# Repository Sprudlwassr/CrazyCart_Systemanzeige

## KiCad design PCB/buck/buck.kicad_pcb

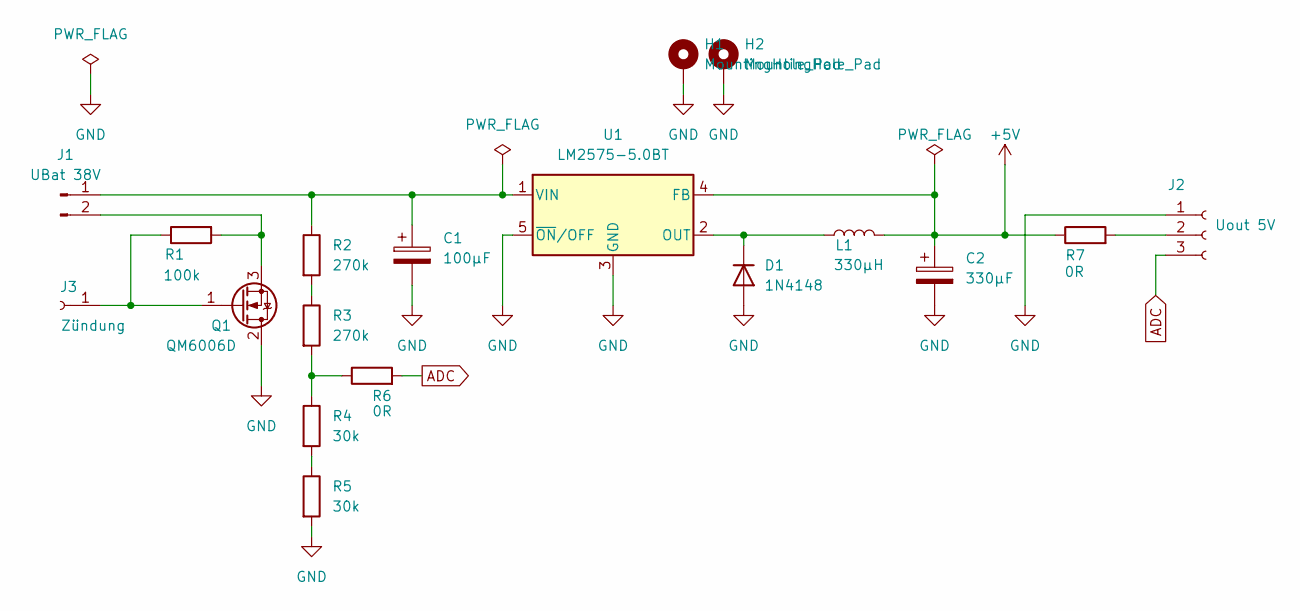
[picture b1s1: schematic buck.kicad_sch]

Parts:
C1: 100µF; CP_Elec_8x10
C2: 330µF; CP_Elec_10x10.5
D1: 1N4148; D_0805_2012Metric_Pad1.15x1.40mm_HandSolder
H1, H2: MountingHole_Pad; MountingHole_2.7mm_M2.5_Pad
J1: UBat 38V; PinSocket_1x02_P2.54mm_Horizontal
J2: Uout 5V; PinSocket_1x03_P2.54mm_Horizontal
J3: Zündung; PinSocket_1x01_P2.54mm_Horizontal
L1: 330µH; L_12x12mm_H8mm
Q1: QM6006D; TO-252-2
R1: 100k; R_0805_2012Metric
R2, R3: 270k; R_0805_2012Metric
R4, R5: 30k; R_0805_2012Metric
R6, R7: 0R; R_0603_1608Metric
U1: LM2575-5.0BT; TO-220-5_Vertical

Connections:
+5V: C2.1, L1.2, R7.1, U1.4 (FB)
ADC: J2.3, R6.2
GND: C1.2, C2.2, D1.1 (A), H1.1, H2.1, J2.1, Q1.2 (D), R5.2, U1.3 (GND), U1.5 (~ON/OFF)
unnamed: C1.1, J1.1, R2.1, U1.1 (VIN)
unnamed: D1.2 (K), L1.1, U1.2 (OUT)
unnamed: J1.2, Q1.3 (S), R1.2
unnamed: J2.2, R7.2
unnamed: J3.1, Q1.1 (G), R1.1
unnamed: R2.2, R3.1
unnamed: R3.2, R4.1, R6.1
unnamed: R4.2, R5.1

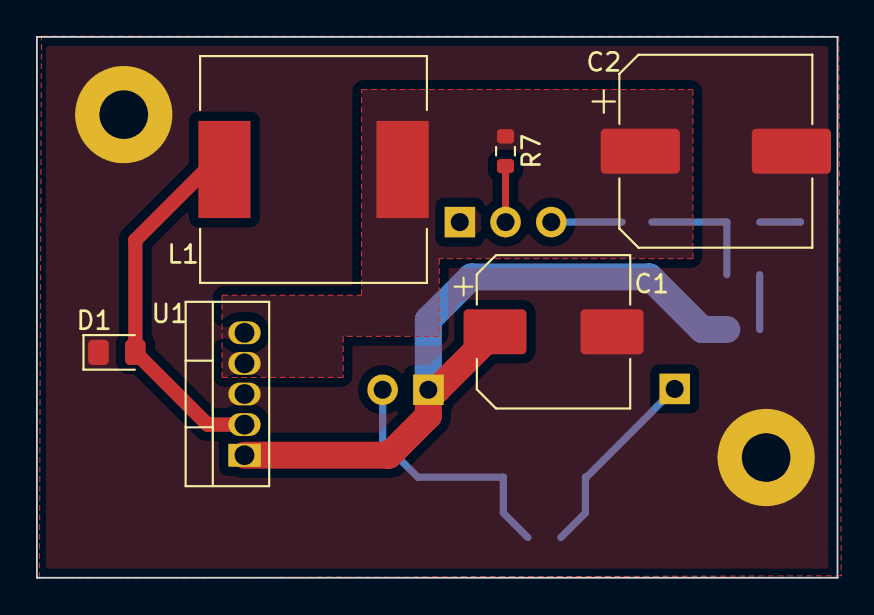
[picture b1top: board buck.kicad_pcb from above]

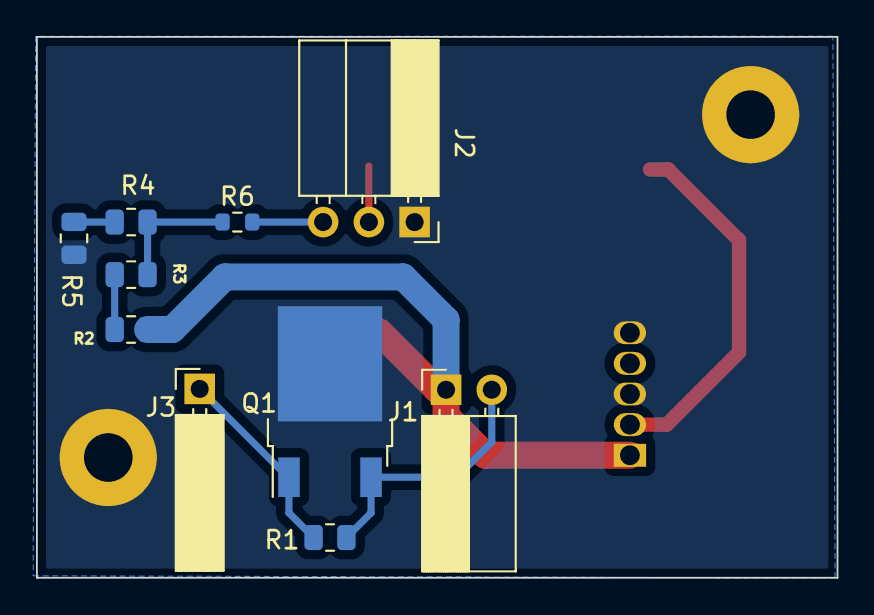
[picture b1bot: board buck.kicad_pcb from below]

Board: 2 copper layers, 44.5 x 30.0 mm, 18 parts (10 on the bottom side), 11 nets.

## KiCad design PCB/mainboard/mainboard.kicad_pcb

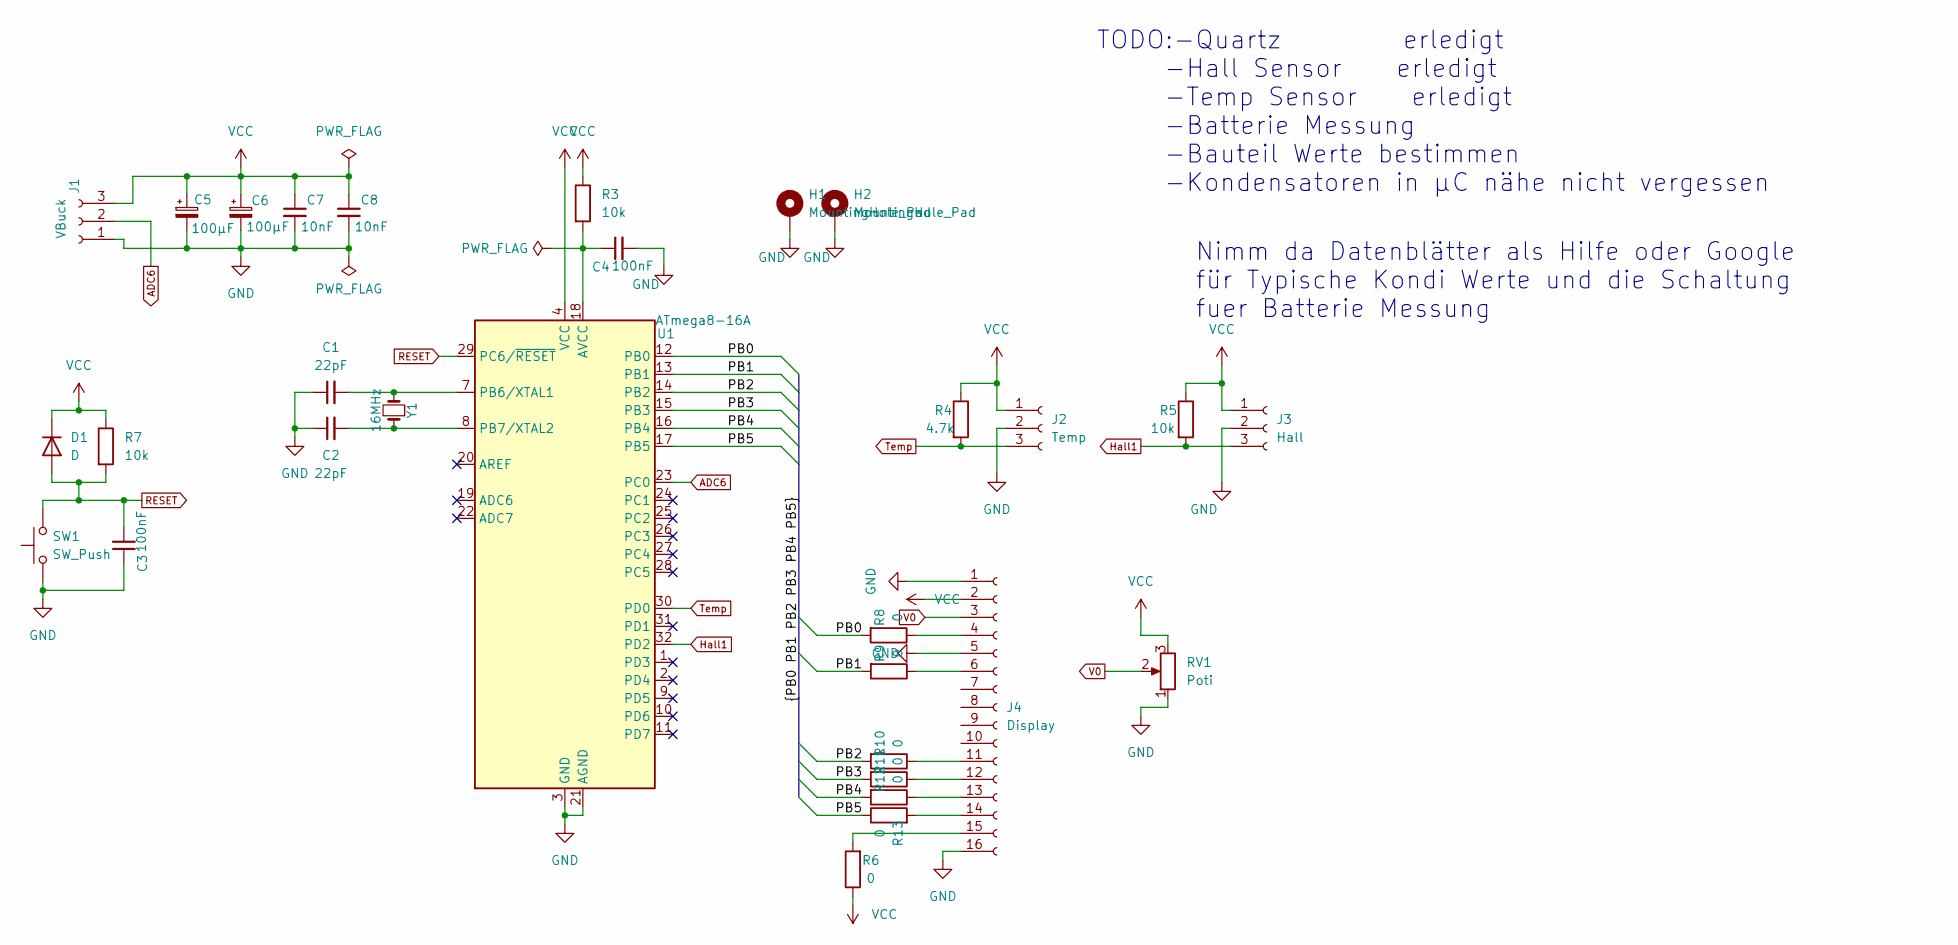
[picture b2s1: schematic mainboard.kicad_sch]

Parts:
C1, C2: 22pF; C_0805_2012Metric
C3, C4: 100nF; C_0805_2012Metric
C5, C6: 100µF; CP_Elec_5x5.8
C7, C8: 10nF; C_0603_1608Metric
D1: D; D_0805_2012Metric
H1, H2: MountingHole_Pad; MountingHole_2.7mm_M2.5_Pad
J1: VBuck; PinSocket_1x03_P2.54mm_Vertical
J2: Temp; PinSocket_1x03_P2.54mm_Horizontal
J3: Hall; PinSocket_1x03_P2.54mm_Horizontal
J4: Display; PinSocket_1x16_P2.54mm_Vertical
R3, R5, R7: 10k; R_0805_2012Metric
R4: 4.7k; R_0805_2012Metric
R6, R8, R9, R10, R11, R12, R13: 0; R_0805_2012Metric
RV1: Poti; Potentiometer_Bourns_3314G_Vertical
SW1: SW_Push; SW_PUSH_6mm
U1: ATmega8-16A; TQFP-32_7x7mm_P0.8mm
Y1: 16MHz; Crystal_SMD_ECS_CSM3X-2Pin_7.6x4.1mm

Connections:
/PB0: R8.2, U1.12 (PB0)
/PB1: R9.2, U1.13 (PB1)
/PB2: R10.2, U1.14 (PB2)
/PB3: R11.2, U1.15 (PB3)
/PB4: R12.2, U1.16 (PB4)
/PB5: R13.1, U1.17 (PB5)
ADC6: J1.2, U1.23 (PC0); also elsewhere on the board
GND: C1.1, C2.1, C3.1, C4.2, C5.2, C6.2, C7.2, C8.2, H1.1, H2.1, J1.1, J2.2, J3.2, J4.1, J4.5, J4.16, RV1.1, SW1.1, U1.3 (GND), U1.5 (GND), U1.21 (AGND); also elsewhere on the board
Hall1: J3.3, R5.2, U1.32 (PD2)
unnamed: C1.2, U1.7 (PB6/XTAL1), Y1.2
unnamed: C2.2, U1.8 (PB7/XTAL2), Y1.1
unnamed: C4.1, R3.2, U1.18 (AVCC)
unnamed: J4.4, R8.1
unnamed: J4.6, R9.1
unnamed: J4.11, R10.1
unnamed: J4.12, R11.1
unnamed: J4.13, R12.1
unnamed: J4.14, R13.2
unnamed: J4.15, R6.2
RESET: C3.2, D1.2 (A), R7.2, SW1.2, U1.29 (PC6/~RESET)
Temp: J2.3, R4.2, U1.30 (PD0)
V0: J4.3, RV1.2
VCC: C5.1, C6.1, C7.1, C8.1, D1.1 (K), J1.3, J2.1, J3.1, J4.2, R3.1, R4.1, R5.1, R6.1, R7.1, RV1.3, U1.4 (VCC), U1.6 (VCC); also elsewhere on the board

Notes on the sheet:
TODO:-Quartz erledigt -Hall Sensor erledigt -Temp Sensor erledigt -Batterie Messung -Bauteil Werte bestimmen -Kondensatoren in µC nähe nicht vergessen
Nimm da Datenblätter als Hilfe oder Google für Typische Kondi Werte und die Schaltung fuer Batterie Messung

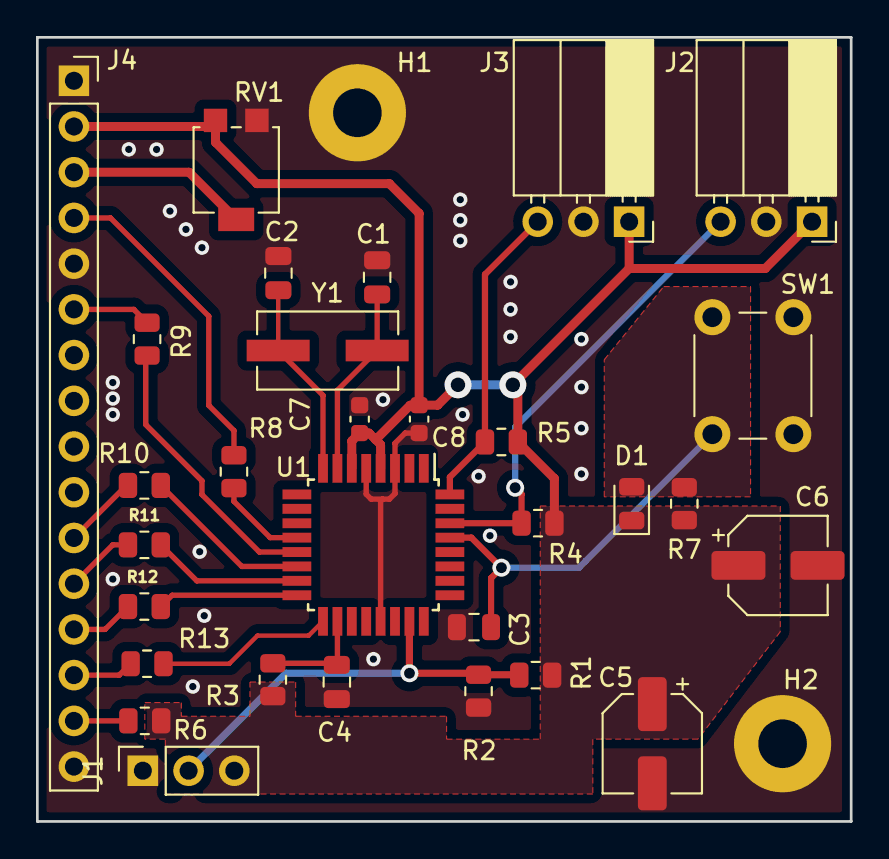
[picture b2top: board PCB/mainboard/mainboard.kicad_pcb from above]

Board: 2 copper layers, 45.2 x 43.6 mm, 32 parts (0 on the bottom side), 23 nets.

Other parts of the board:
R1: 99k; R_0805_2012Metric
R2: 11k; R_0805_2012Metric

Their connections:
ADC6: R1.2, R2.1; also elsewhere on the board
GND: R2.2; also elsewhere on the board
VCC: R1.1; also elsewhere on the board

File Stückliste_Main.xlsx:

|  |  |  |  |  |  |  |  | Höhere technische Bundeslehr- und Versuchsanstalt Rankweil
 |  |  |  |  |  |  |  |  | Abteilung Elektronik
 |  |  |  | Projektname: | Nummer | Betreuungslehrer
 |  |  |  | Alarmanlage 2AFEL 21-22 | n.a. | MM/SCHN
STÜCKLISTE |  |  |  |  |  | SUMME |  | 0
Pos | Stück | Wert | Benennung | Text / Bauform | Quelle | Best.Nr | Preis | Gesamt | Bemerkung
1 | 2 | 22pF | C1,2 | SMD_0805 |  |  |  | 0
2 | 1 | 100nF | C4 | SMD_0805 |  |  |  | 0
3 | 2 | 100µF | C5,6 | SMD_Elco_5x5.8 |  |  |  | 0
4 | 2 | 10nF | C7,8 | SMD_0603 |  |  |  | 0
5 | 1 | Vbuck | J1 | 2.54mm:PinSocket_1x02_Vertical |  |  |  | 0
6 | 2 | Temp,Hall | J2,3 | 2.54mm:PinSocket_1x03_Horizontal |  |  |  | 0
7 | 1 | Display | J4 | 2.54mm:PinSocket_1x16_Vertical |  |  |  | 0
8 | 1 | 99k | R1 | SMD_0805 |  |  |  | 0
9 | 1 | 11k | R2 | SMD_0805 |  |  |  | 0
10 | 2 | 10k | R3,5 | SMD_0805 |  |  |  | 0
11 | 1 | 4.7k | R4 | SMD_0805 |  |  |  | 0
12 | 1 | 0R | R6 | SMD_0805 |  |  |  | 0
13 | 1 | Poti | RV1 | Ppotentiometer_Bourns_3314G_Vertical |  |  |  | 0
14 | 1 | Atmega8-16A | U1 | TQFP-32_7x7mm_P00.8mm |  |  |  | 0
15 | 1 | Y1 | 16MHz | 2pin_7.6x7.1mm |  |  |  | 0
16 |  |  |  |  |  |  |  | 0
17 |  |  |  |  |  |  |  | 0
18 |  |  |  |  |  |  |  | 0
19 |  |  |  |  |  |  |  | 0
20 |  |  |  |  |  |  |  | 0
21 |  |  |  |  |  |  |  | 0
22 |  |  |  |  |  |  |  | 0
23 |  |  |  |  |  |  |  | 0
24 |  |  |  |  |  |  |  | 0
25 |  |  |  |  |  |  |  | 0
26 |  |  |  |  |  |  |  | 0
27 |  |  |  |  |  |  |  | 0
28 |  |  |  |  |  |  |  | 0
29 |  |  |  |  |  |  |  | 0

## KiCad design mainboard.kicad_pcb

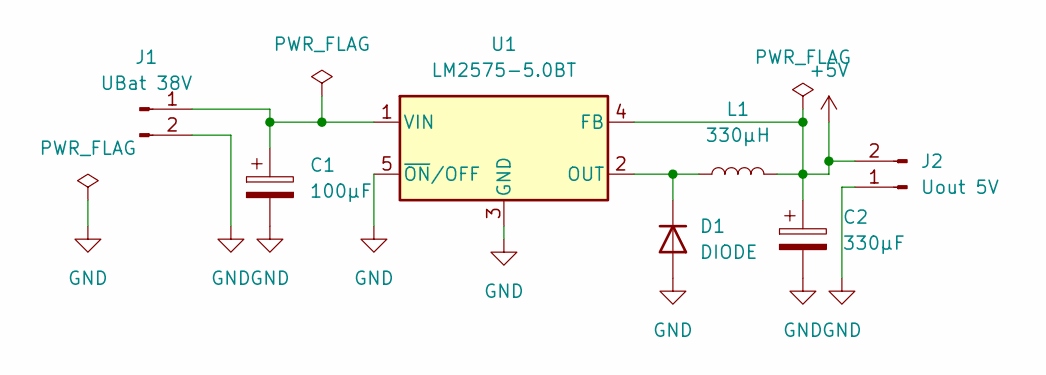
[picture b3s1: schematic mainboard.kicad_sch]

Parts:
C1: 100µF; CP_Elec_8x10
C2: 330µF; CP_Elec_10x10.5
D1: DIODE; D_0805_2012Metric_Pad1.15x1.40mm_HandSolder
J1: UBat 38V; PinHeader_1x02_P2.00mm_Horizontal
J2: Uout 5V; PinHeader_1x02_P2.00mm_Vertical
L1: 330µH; L_12x12mm_H8mm
U1: LM2575-5.0BT; TO-220-5_Vertical

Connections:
+5V: C2.1, J2.2, L1.2, U1.4 (FB)
GND: C1.2, C2.2, D1.1 (A), J1.2, J2.1, U1.3 (GND), U1.5 (~ON/OFF)
unnamed: C1.1, J1.1, U1.1 (VIN)
unnamed: D1.2 (K), L1.1, U1.2 (OUT)

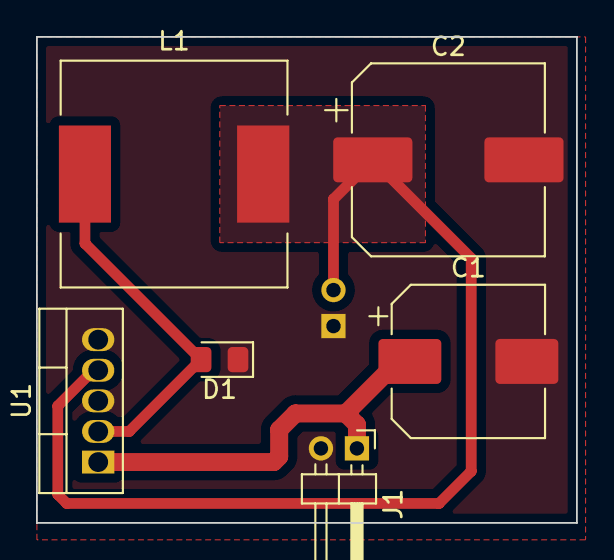
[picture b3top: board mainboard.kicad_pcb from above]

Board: 2 copper layers, 30.0 x 27.0 mm, 7 parts (1 on the bottom side), 4 nets.

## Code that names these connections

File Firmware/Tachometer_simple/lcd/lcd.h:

/* -----------------------------------------
 * G.Raf^engineering
 * www.sunriax.at
 * -----------------------------------------
 *    Platform: Megacard/STK500/STK600
 *    Hardware: ATmega??-????
 * -----------------------------------------
 *     Version: 1.0 Release
 *      Author: G.Raf
 * Description:
 *   Header file for lcd library
 * -----------------------------------------
 */

#ifndef LCD_H_
#define LCD_H_

// Definition of SYSTEM parameters

#ifndef F_CPU           // System clock
    #define F_CPU 12000000UL
#endif

// Definition of LCD parameters

#ifndef F_LCD           // LCD enable clock
    #define F_LCD 100000UL
#endif

// LCD control directives
#ifndef LCD_DDR_CTRL    // LCD control direction register
    #define LCD_DDR_CTRL DDRB
#endif

#ifndef LCD_PORT_CTRL   // LCD control port register
    #define LCD_PORT_CTRL PORTB
#endif

#ifndef LCD_RS          // LCD register select
    #define LCD_RS PB0
#endif

#ifndef LCD_E           // LCD start data read/write
    #define LCD_E PB1
#endif

// LCD data directives
#ifndef LCD_DDR_DATA    // LCD data direction register
    #define LCD_DDR_DATA DDRB
#endif

#ifndef LCD_PORT_DATA   // LCD control direction register
    #define LCD_PORT_DATA PORTB
#endif

#ifndef LCD_DB0         // LCD data bit 0 (LCD display bit 4)
    #define LCD_DB0 PB2
#endif

#ifndef LCD_DB1         // LCD data bit 1 (LCD display bit 5)
    #define LCD_DB1 PB3
#endif

#ifndef LCD_DB2         // LCD data bit 2 (LCD display bit 6)
    #define LCD_DB2 PB4
#endif

#ifndef LCD_DB3         // LCD data bit 3 (LCD display bit 7)
    #define LCD_DB3 PB5
#endif

// LCD display parameters
#ifndef LCD_COLUMNS     // LCD display columns/row (1 - 20)
    #define LCD_COLUMNS 20
#endif

#ifndef LCD_COLUMNS_END     // LCD character memory length
    #define LCD_COLUMNS_END 40
#endif

#ifndef LCD_START_ADDR      // Start position of the LCD RAM
    #define LCD_START_ADDR 0x80
#endif

// LCD time/instruction codes (!!! Do not change !!!)

// LCD time directives
#ifndef LCD_STARTUP_TIME    // LCD startup time in ms
    #define LCD_STARTUP_TIME 10
#endif

#ifndef LCD_RETURN_TIME     // LCD return home time in ms
    #define LCD_RETURN_TIME 2
#endif

#ifndef LCD_ENTRY_TIME      // LCD entry mode time in us
    #define LCD_ENTRY_TIME 37
#endif

// #ifndef LCD_DISPLAY_TIME // LCD display time in us
//  #define LCD_DISPLAY_TIME 37
// #endif

#ifndef LCD_SHIFT_TIME      // LCD shift time in us
    #define LCD_SHIFT_TIME 37
#endif

#ifndef LCD_FUNCTION_TIME   // LCD function time in us
    #define LCD_FUNCTION_TIME 37
#endif

#ifndef LCD_WRITE_TIME      // LCD WRITE time in us
    #define LCD_WRITE_TIME 37
#endif

#ifndef LCD_CMD_TIME        // LCD COMMAND time in us
    #define LCD_CMD_TIME 37
#endif

// LCD instruction directives
#ifndef LCD_CLEAR           // LCD clear display instruction
    #define LCD_CLEAR           0b00000001
#endif

#ifndef LCD_HOME            // LCD return home instruction
    #define LCD_HOME            0b00000010
#endif

#ifndef LCD_ENTRY           // LCD entry mode set instruction
    #define LCD_ENTRY           0b00000100
    #define LCD_ENTRY_INCREMENT 0b00000010
    #define LCD_ENTRY_SHIFT     0b00000001
#endif

#ifndef LCD_DISPLAY         // LCD display set instruction
    #define LCD_DISPLAY         0b00001000
    #define LCD_DISPLAY_ON      0b00000100
    #define LCD_CURSOR_ON       0b00000010
    #define LCD_BLINK_ON        0b00000001
#endif

#ifndef LCD_SHIFT           // LCD shift instruction
    #define LCD_SHIFT           0b00010000
    #define LCD_SHIFT_DISPLAY   0b00001000
    #define LCD_SHIFT_RIGHT     0b00000100
#endif

#ifndef LCD_FUNCTION        // LCD function instruction
    #define LCD_FUNCTION        0b00100000
    #define LCD_FUNCTION_8BIT   0b00010000
    #define LCD_FUNCTION_2LINE  0b00001000
    #define LCD_FUNCTION_5x10   0b00000100
#endif

#ifndef LCD_CGADDR          // LCD CGADDR instruction
    #define LCD_CGADDR          0b01000000
    #define LCD_CGADDR_CHAR0    0b00000000
    #define LCD_CGADDR_CHAR1    0b00000001
    #define LCD_CGADDR_CHAR2    0b00000010
    #define LCD_CGADDR_CHAR3    0b00000011
    #define LCD_CGADDR_CHAR4    0b00000100
    #define LCD_CGADDR_CHAR5    0b00000101
    #define LCD_CGADDR_CHAR6    0b00000110
    #define LCD_CGADDR_CHAR7    0b00000111
    #define LCD_CGADDDR_MAX     7
#endif

#ifndef LCD_DDADDR          // LCD DDADDR instruction
    #define LCD_DDADDR          0b10000000
#endif

#ifndef LCD_SPACE           // Space character
    #define LCD_SPACE 0x20
#endif

#ifndef LCD_NULL            // End character
    #define LCD_NULL 0x00
#endif

#include <stdlib.h>
#include <avr/io.h>
#include <util/delay.h>

enum LCD_Shift_t
{
    LCD_Right=0,
    LCD_Left
};
typedef enum LCD_Shift_t LCD_Shift;

enum LCD_Base_t
{
    LCD_Binary=2,
    LCD_Decimal=10,
    LCD_Hexadecimal=16    
};
typedef enum LCD_Base_t LCD_Base;

enum LCD_Char_t
{
    LCD_Char0=LCD_CGADDR_CHAR0,
    LCD_Char1=LCD_CGADDR_CHAR1,
    LCD_Char2=LCD_CGADDR_CHAR2,
    LCD_Char3=LCD_CGADDR_CHAR3,
    LCD_Char4=LCD_CGADDR_CHAR4,
    LCD_Char5=LCD_CGADDR_CHAR5,
    LCD_Char6=LCD_CGADDR_CHAR6,
    LCD_Char7=LCD_CGADDR_CHAR7
};
typedef enum LCD_Char_t LCD_Char;

void lcd_init(void);
void lcd_disable(void);
void lcd_clock(void);
void lcd_set(unsigned char data);
void lcd_cmd(unsigned char instruction);
void lcd_char(unsigned char data);
void lcd_string(const char *data);
void lcd_clear(void);
void lcd_home(void);
void lcd_cursor(unsigned char x, unsigned char y);
void lcd_shift(LCD_Shift shift);
void lcd_pattern(LCD_Char address, const unsigned char *data);
void lcd_ul2ascii(unsigned long data, LCD_Base base, unsigned char length);
void lcd_sl2ascii(const signed long data, LCD_Base base, unsigned char length);
void lcd_d2ascii(const double data, signed char length, unsigned char precision);

#endif /* LCD_H_ */

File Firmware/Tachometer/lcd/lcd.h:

/* -----------------------------------------
 * G.Raf^engineering
 * www.sunriax.at
 * -----------------------------------------
 *    Platform: Megacard/STK500/STK600
 *    Hardware: ATmega??-????
 * -----------------------------------------
 *     Version: 1.0 Release
 *      Author: G.Raf
 * Description:
 *   Header file for lcd library
 * -----------------------------------------
 */

#ifndef LCD_H_
#define LCD_H_

// Definition of SYSTEM parameters

#ifndef F_CPU           // System clock
    #define F_CPU 12000000UL
#endif

// Definition of LCD parameters

#ifndef F_LCD           // LCD enable clock
    #define F_LCD 100000UL
#endif

// LCD control directives
#ifndef LCD_DDR_CTRL    // LCD control direction register
    #define LCD_DDR_CTRL DDRA
#endif

#ifndef LCD_PORT_CTRL   // LCD control port register
    #define LCD_PORT_CTRL PORTA
#endif

#ifndef LCD_RS          // LCD register select
    #define LCD_RS PA6
#endif

#ifndef LCD_E           // LCD start data read/write
    #define LCD_E PA4
#endif

// LCD data directives
#ifndef LCD_DDR_DATA    // LCD data direction register
    #define LCD_DDR_DATA DDRB
#endif

#ifndef LCD_PORT_DATA   // LCD control direction register
    #define LCD_PORT_DATA PORTB
#endif

#ifndef LCD_DB0         // LCD data bit 0 (LCD display bit 4)
    #define LCD_DB0 PB2
#endif

#ifndef LCD_DB1         // LCD data bit 1 (LCD display bit 5)
    #define LCD_DB1 PB5
#endif

#ifndef LCD_DB2         // LCD data bit 2 (LCD display bit 6)
    #define LCD_DB2 PB6
#endif

#ifndef LCD_DB3         // LCD data bit 3 (LCD display bit 7)
    #define LCD_DB3 PB7
#endif

// LCD display parameters
#ifndef LCD_COLUMNS     // LCD display columns/row (1 - 20)
    #define LCD_COLUMNS 8
#endif

#ifndef LCD_COLUMNS_END     // LCD character memory length
    #define LCD_COLUMNS_END 80
#endif

#ifndef LCD_START_ADDR      // Start position of the LCD RAM
    #define LCD_START_ADDR 0x80
#endif

// LCD time/instruction codes (!!! Do not change !!!)

// LCD time directives
#ifndef LCD_STARTUP_TIME    // LCD startup time in ms
    #define LCD_STARTUP_TIME 10
#endif

#ifndef LCD_RETURN_TIME     // LCD return home time in ms
    #define LCD_RETURN_TIME 2
#endif

#ifndef LCD_ENTRY_TIME      // LCD entry mode time in us
    #define LCD_ENTRY_TIME 37
#endif

// #ifndef LCD_DISPLAY_TIME // LCD display time in us
//  #define LCD_DISPLAY_TIME 37
// #endif

#ifndef LCD_SHIFT_TIME      // LCD shift time in us
    #define LCD_SHIFT_TIME 37
#endif

#ifndef LCD_FUNCTION_TIME   // LCD function time in us
    #define LCD_FUNCTION_TIME 37
#endif

#ifndef LCD_WRITE_TIME      // LCD WRITE time in us
    #define LCD_WRITE_TIME 37
#endif

#ifndef LCD_CMD_TIME        // LCD COMMAND time in us
    #define LCD_CMD_TIME 37
#endif

// LCD instruction directives
#ifndef LCD_CLEAR           // LCD clear display instruction
    #define LCD_CLEAR           0b00000001
#endif

#ifndef LCD_HOME            // LCD return home instruction
    #define LCD_HOME            0b00000010
#endif

#ifndef LCD_ENTRY           // LCD entry mode set instruction
    #define LCD_ENTRY           0b00000100
    #define LCD_ENTRY_INCREMENT 0b00000010
    #define LCD_ENTRY_SHIFT     0b00000001
#endif

#ifndef LCD_DISPLAY         // LCD display set instruction
    #define LCD_DISPLAY         0b00001000
    #define LCD_DISPLAY_ON      0b00000100
    #define LCD_CURSOR_ON       0b00000010
    #define LCD_BLINK_ON        0b00000001
#endif

#ifndef LCD_SHIFT           // LCD shift instruction
    #define LCD_SHIFT           0b00010000
    #define LCD_SHIFT_DISPLAY   0b00001000
    #define LCD_SHIFT_RIGHT     0b00000100
#endif

#ifndef LCD_FUNCTION        // LCD function instruction
    #define LCD_FUNCTION        0b00100000
    #define LCD_FUNCTION_8BIT   0b00010000
    #define LCD_FUNCTION_2LINE  0b00001000
    #define LCD_FUNCTION_5x10   0b00000100
#endif

#ifndef LCD_CGADDR          // LCD CGADDR instruction
    #define LCD_CGADDR          0b01000000
    #define LCD_CGADDR_CHAR0    0b00000000
    #define LCD_CGADDR_CHAR1    0b00000001
    #define LCD_CGADDR_CHAR2    0b00000010
    #define LCD_CGADDR_CHAR3    0b00000011
    #define LCD_CGADDR_CHAR4    0b00000100
    #define LCD_CGADDR_CHAR5    0b00000101
    #define LCD_CGADDR_CHAR6    0b00000110
    #define LCD_CGADDR_CHAR7    0b00000111
    #define LCD_CGADDDR_MAX     7
#endif

#ifndef LCD_DDADDR          // LCD DDADDR instruction
    #define LCD_DDADDR          0b10000000
#endif

#ifndef LCD_SPACE           // Space character
    #define LCD_SPACE 0x20
#endif

#ifndef LCD_NULL            // End character
    #define LCD_NULL 0x00
#endif

#include <stdlib.h>
#include <avr/io.h>
#include <util/delay.h>

enum LCD_Shift_t
{
    LCD_Right=0,
    LCD_Left
};
typedef enum LCD_Shift_t LCD_Shift;

enum LCD_Base_t
{
    LCD_Binary=2,
    LCD_Decimal=10,
    LCD_Hexadecimal=16    
};
typedef enum LCD_Base_t LCD_Base;

enum LCD_Char_t
{
    LCD_Char0=LCD_CGADDR_CHAR0,
    LCD_Char1=LCD_CGADDR_CHAR1,
    LCD_Char2=LCD_CGADDR_CHAR2,
    LCD_Char3=LCD_CGADDR_CHAR3,
    LCD_Char4=LCD_CGADDR_CHAR4,
    LCD_Char5=LCD_CGADDR_CHAR5,
    LCD_Char6=LCD_CGADDR_CHAR6,
    LCD_Char7=LCD_CGADDR_CHAR7
};
typedef enum LCD_Char_t LCD_Char;

void lcd_init(void);
void lcd_disable(void);
void lcd_clock(void);
void lcd_set(unsigned char data);
void lcd_cmd(unsigned char instruction);
void lcd_char(unsigned char data);
void lcd_string(const char *data);
void lcd_clear(void);
void lcd_home(void);
void lcd_cursor(unsigned char x, unsigned char y);
void lcd_shift(LCD_Shift shift);
void lcd_pattern(LCD_Char address, const unsigned char *data);
void lcd_ul2ascii(unsigned long data, LCD_Base base, unsigned char length);
void lcd_sl2ascii(const signed long data, LCD_Base base, unsigned char length);
void lcd_d2ascii(const double data, signed char length, unsigned char precision);

#endif /* LCD_H_ */

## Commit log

2022-11-10 File and folder organisation
2022-11-10 Create directories and move files
2022-11-27 Rename Template_HTL_Rankweil_Display_V31.cproj to FW0001.cproj
2022-11-27 Rename Template_HTL_Rankweil_Display_V31.componentinfo.xml to FW0001.componentinfo.xml
2022-11-27 Rename Template_HTL_Rankweil_Display_V31.atsln to Firmware.atsln
2022-11-30 Rename FW0001.componentinfo.xml to tachometer.componentinfo.xml
2022-11-30 Rename FW0001.cproj to Tachometer.cproj
2022-11-30 Rename Firmware/FW0001/Tachometer.cproj to Firmware/Tachometer/Tachometer.cproj
2022-11-30 Rename Firmware/FW0001/main.c to Firmware/Tachometer/main.c
2022-11-30 Rename Firmware/FW0001/tachometer.componentinfo.xml to Firmware/Tachometer/tachometer.componentinfo.xml
2022-11-30 Rename Firmware/Firmware.atsln to Firmware/Tachometer/Firmware.atsln
2022-11-30 Rename Firmware/main.c to Firmware/DS18B20_Temp/main.c
2022-11-30 Rename Firmware/Temp_ds18b20.componentinfo.xml to Firmware/DS18B20_Temp/Temp_ds18b20.componentinfo.xml
2022-11-30 Rename Firmware/ds18b20.c to Firmware/DS18B20_LIB/ds18b20.c
2022-11-30 Rename Firmware/Display/display.h to Firmware/DISPLAY_LIB/display.h
2022-12-07 Project refactoring
2022-12-07 Fix missing PCB
2022-12-11 Create test
2022-12-14 Create d
2022-12-23 PCB error correction
2023-03-08 Release v1.0
